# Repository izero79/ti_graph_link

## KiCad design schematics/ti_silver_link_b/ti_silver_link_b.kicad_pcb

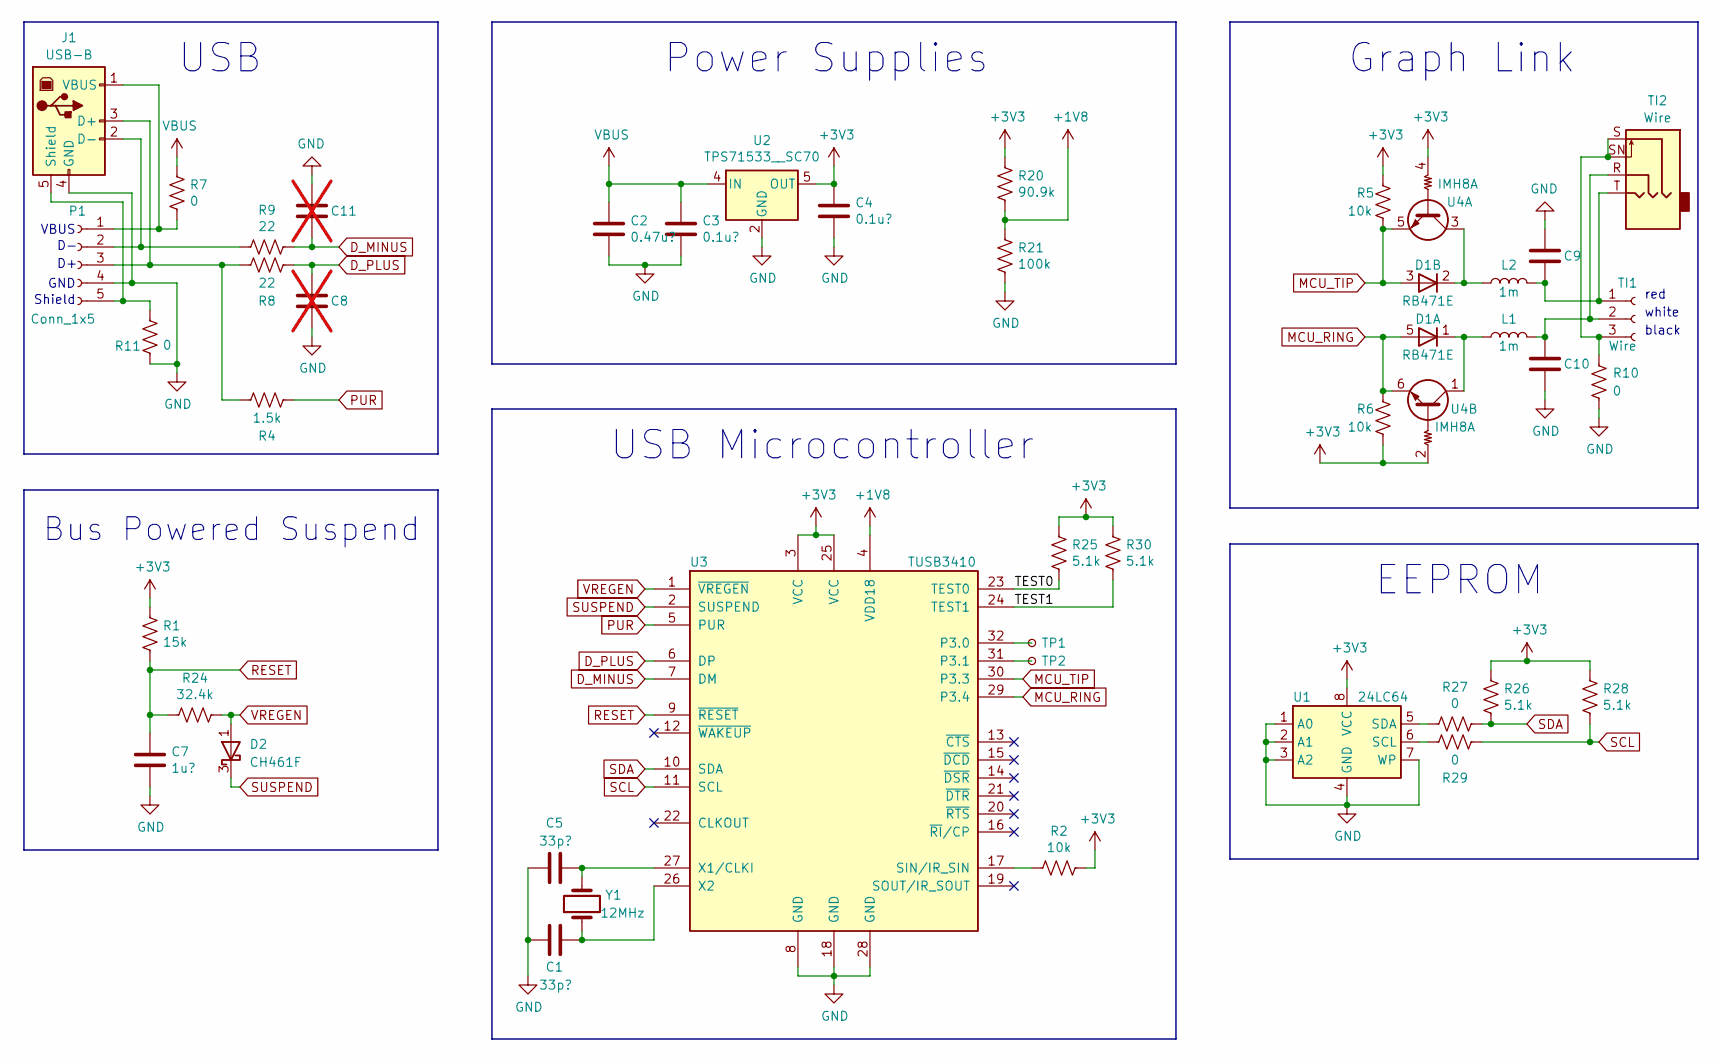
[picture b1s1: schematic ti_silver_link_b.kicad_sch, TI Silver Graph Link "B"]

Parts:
C1, C5: 33p?; C_0805_2012Metric_Pad1.18x1.45mm_HandSolder
C2: 0.47u?; C_0805_2012Metric_Pad1.18x1.45mm_HandSolder
C3, C4: 0.1u?; C_0805_2012Metric_Pad1.18x1.45mm_HandSolder
C7: 1u?; C_0805_2012Metric_Pad1.18x1.45mm_HandSolder
C8, C11: C_0805_2012Metric_Pad1.18x1.45mm_HandSolder; not fitted
C9, C10: C_0805_2012Metric_Pad1.18x1.45mm_HandSolder
D1: RB471E; SOT-25_HandSoldering_clockwise_pin_numbering
D2: CH461F; SOT-323_SC-70
J1: USB-B; USB_B_Logitech_C270_cable_connector
L1, L2: 1m; L_0805_2012Metric_Pad1.05x1.20mm_HandSolder
P1: Conn_1x5; PinHeader_1x05_P2.54mm_Vertical
R1: 15k; R_0805_2012Metric_Pad1.20x1.40mm_HandSolder
R2, R5, R6: 10k; R_0805_2012Metric_Pad1.20x1.40mm_HandSolder
R4: 1.5k; R_0805_2012Metric_Pad1.20x1.40mm_HandSolder
R7, R10, R11, R27, R29: 0; R_0805_2012Metric_Pad1.20x1.40mm_HandSolder
R8, R9: 22; R_0805_2012Metric_Pad1.20x1.40mm_HandSolder
R20: 90.9k; R_0805_2012Metric_Pad1.20x1.40mm_HandSolder
R21: 100k; R_0805_2012Metric_Pad1.20x1.40mm_HandSolder
R24: 32.4k; R_0805_2012Metric_Pad1.20x1.40mm_HandSolder
R25, R26, R28, R30: 5.1k; R_0805_2012Metric_Pad1.20x1.40mm_HandSolder
TI1: Wire; PinHeader_1x03_P2.54mm_Vertical
TI2: Wire; Jack_2.5mm_with_switch-SMT_Horizontal
TP1, TP2: TestPoint_Pad_D1.0mm
U1: 24LC64; SOIC-8_3.9x4.9mm_P1.27mm
U2: TPS71533__SC70; SOT-353_SC-70-5
U3: TUSB3410; LQFP-32_7x7mm_P0.8mm
U4: IMH8A; ROHM_SOT-457_ClockwisePinNumbering
Y1: 12MHz; Crystal_SMD_HC49-SD

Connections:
+1V8: R20.2, R21.1, U3.4 (VDD18)
+3V3: C4.1, R1.1, R2.1, R5.1, R6.2, R20.1, R25.1, R26.1, R28.1, R30.1, U1.8 (VCC), U2.5 (OUT), U3.3 (VCC), U3.25 (VCC), U4.2 (B1), U4.4 (B1)
/TEST0: R25.2, U3.23 (TEST0)
/TEST1: R30.2, U3.24 (TEST1)
D_MINUS: C11.2, R9.1, U3.7 (DM)
D_PLUS: C8.1, R8.1, U3.6 (DP)
GND: C1.1, C2.2, C3.2, C4.2, C5.1, C7.2, C8.2, C9.1, C10.2, C11.1, J1.4 (GND), P1.4, R10.2, R11.2, R21.2, U1.1 (A0), U1.2 (A1), U1.3 (A2), U1.4 (GND), U1.7 (WP), U2.2 (GND), U3.8 (GND), U3.18 (GND), U3.28 (GND)
MCU_RING: D1.5, R6.1, U3.29 (P3.4), U4.6 (E1)
MCU_TIP: D1.3, R5.2, U3.30 (P3.3), U4.5 (E1)
unnamed: J1.3 (D+), P1.3, R4.2, R8.2
unnamed: J1.2 (D-), P1.2, R9.2
unnamed: J1.5 (Shield), P1.5, R11.1
unnamed: J1.1 (VBUS), P1.1, R7.2
unnamed: C9.2, L2.2, TI1.1, TI2.T
unnamed: C10.1, L1.2, TI1.2, TI2.R
unnamed: R10.1, TI1.3, TI2.S, TI2.SN
unnamed: R29.2, U1.6 (SCL)
unnamed: R27.2, U1.5 (SDA)
unnamed: TP1.1, U3.32 (P3.0)
unnamed: TP2.1, U3.31 (P3.1)
unnamed: R2.2, U3.17 (SIN/IR_SIN)
unnamed: C5.2, U3.27 (X1/CLKI), Y1.2
unnamed: C1.2, U3.26 (X2), Y1.1
unnamed: D1.2, L2.1, U4.3 (C1)
unnamed: D1.1, L1.1, U4.1 (C1)
PUR: R4.1, U3.5 (PUR)
RESET: C7.1, R1.2, R24.2, U3.9 (~RESET)
SCL: R28.2, R29.1, U3.11 (SCL)
SDA: R26.2, R27.1, U3.10 (SDA)
SUSPEND: D2.3 (K), U3.2 (SUSPEND)
VBUS: C2.1, C3.1, R7.1, U2.4 (IN)
VREGEN: D2.1 (A), R24.1, U3.1 (~VREGEN)

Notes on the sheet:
red
Bus Powered Suspend
GND
white
USB Microcontroller
Shield
VBUS
black
Graph Link
USB
EEPROM
Power Supplies

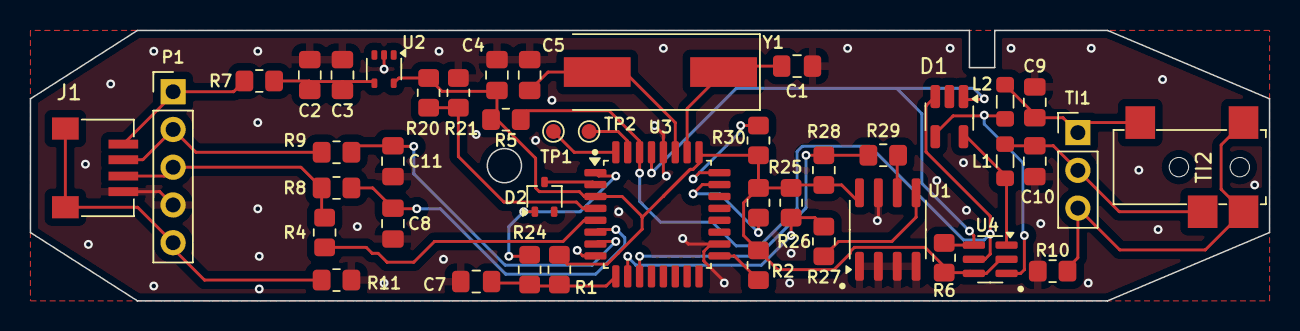
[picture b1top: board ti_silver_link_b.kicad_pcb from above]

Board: 2 copper layers, 83.4 x 18.2 mm, 44 parts (0 on the bottom side), 32 nets.

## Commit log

2024-03-12 Add footprints to "B" schematic's components and add initial pcb layout
2024-06-12 Update and fix "B" schematic's footprints and layout
    Wrong pinout was used in U4 and D1
2024-06-13 Add missing footprint library to schematic "B"
2024-06-13 Add USB and audio jack connectors to "B" schematic and pcb layout
